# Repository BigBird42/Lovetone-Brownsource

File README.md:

# Lovetone-Brownsource

This is a kicad pcb layout for the Lovetone Brownsource guitar pedal. The original schematic can be found here: http://bmamps.com/Schematics/Effects_miscellaneous/Lovetone_BrownSource.gif.

A description for the pedal can be found here:http://www.lovetone.com/bsource.html.

I've modified the schematic to use a 10uF film cap for C2 and to include footprints for a 3PDT footswitch with an LED indicator. A Bill of Materials will be added soon. 

You can see a copy of the PCB on OSHpark here:https://oshpark.com/profiles/BigBird42.

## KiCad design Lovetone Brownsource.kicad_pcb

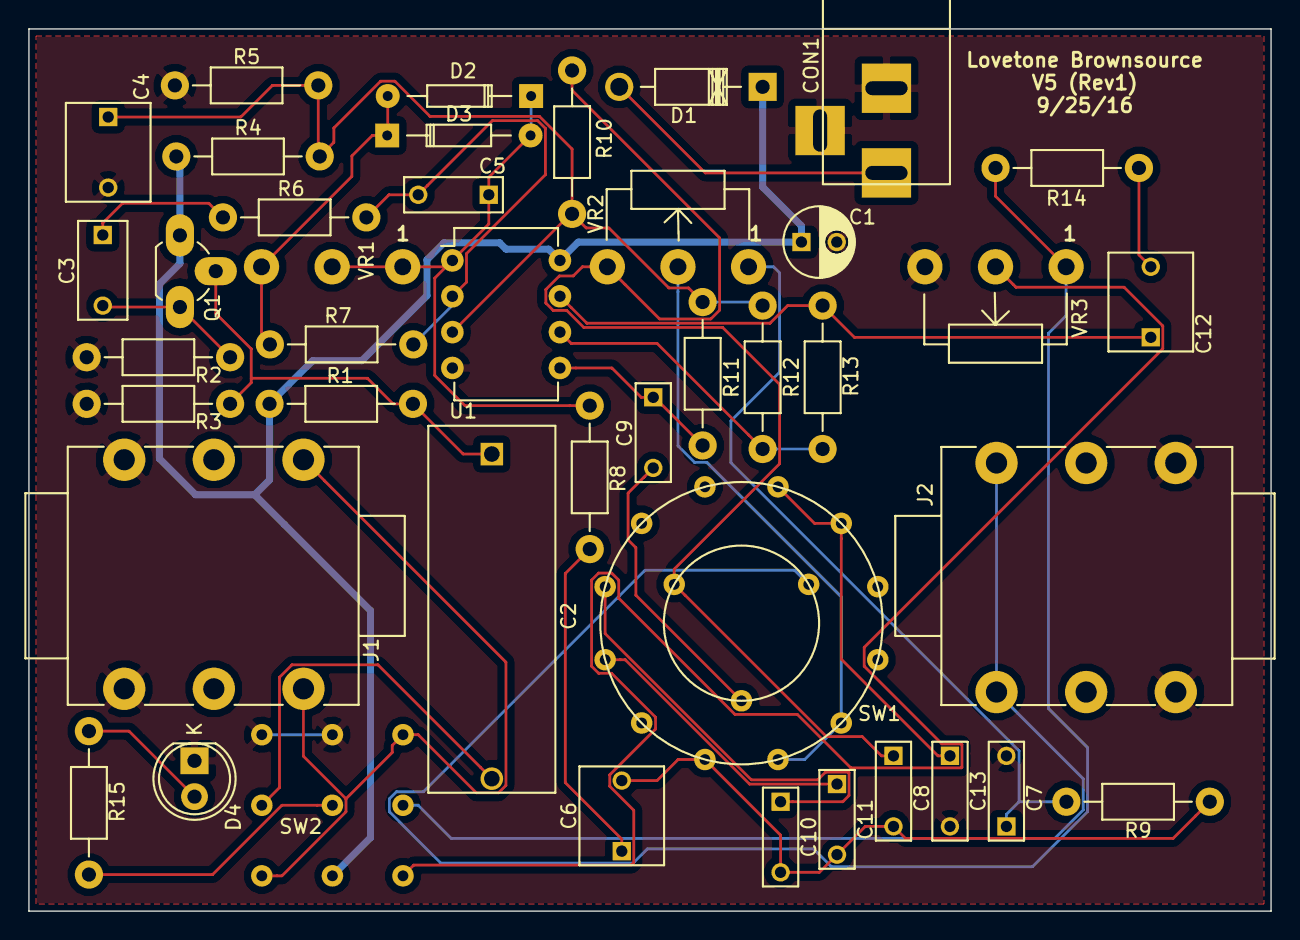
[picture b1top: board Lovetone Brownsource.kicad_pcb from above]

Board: 2 copper layers, 88.0 x 62.5 mm, 42 parts (1 on the bottom side), 30 nets.

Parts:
C1: 47uF; C_Radial_D5_L6_P2.5
C2: 10uF; C_Rect_L27_W9_H17_P23
C3: 47nF; C_Rect_L7_W3.5_P5
C4, C6, C12: 4.7uF; C_Rect_L7_W6_P5
C5, C7, C8, C10, C13: 33nF; C_Rect_L7_W2.5_P5
C9, C11: 22nF; C_Rect_L7_W2.5_P5
CON1: BARREL_JACK
D1: 1N4001; Diode_DO-41_SOD81_Horizontal_RM10
D2, D3: 1N4148; Diode_DO-35_SOD27_Horizontal_RM10
D4: LED; LED-5MM
J1, J2: JACK_TRS_6PINS; NMJ6HCD2
Q1: BC549; TO-92_Rugged
R1, R2: 1M2; Resistor_Horizontal_RM10mm
R3, R9, R10, R12: 3k9; Resistor_Horizontal_RM10mm
R4, R5, R13: 22k; Resistor_Horizontal_RM10mm
R6, R14: 220E; Resistor_Horizontal_RM10mm
R7, R8: 1k; Resistor_Horizontal_RM10mm
R11: 330k; Resistor_Horizontal_RM10mm
R15: 2k2; Resistor_Horizontal_RM10mm
SW1: Rotary_3P4T; Rotarysw0304
SW2: footsw3P2T; footsw_3PDT
U1: NE5532; DIP-8_W7.62mm
VR1: 25k; Potentiometer_WirePads
VR2: 100k; Potentiometer_WirePads
VR3: 10k; Potentiometer_WirePads

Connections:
GND: C1.2, C4.2, C7.2, C13.2, CON1.2, CON1.3, D4.1, J1.1, J1.4, J2.1, J2.4, R2.2, R3.2, R5.2, SW2.3, SW2.6, U1.4, VR3.3
unnamed: C2.1, Q1.2, R1.2, R2.1
unnamed: C2.2, SW2.2
unnamed: C3.1, R6.2
unnamed: C3.2, Q1.3, R3.1
unnamed: C4.1, R4.2, R5.1, R10.1, R11.1, R12.1, U1.3
unnamed: C5.1, D2.1, D3.2, R8.2, U1.1, VR1.1, VR1.2
unnamed: C5.2, R6.1, R7.1, U1.2
unnamed: C6.1, R8.1
unnamed: C7.1, R9.1, VR2.3
unnamed: C8.1, R10.2, SW1.1, VR2.1
unnamed: C9.1, R11.2, U1.5
unnamed: C9.2, SW1.6
unnamed: C10.1, SW1.3
unnamed: C6.2, C8.2, C10.2, C11.2, R9.2, SW1.7
unnamed: C11.1, SW1.4
unnamed: C12.1, R13.1, U1.7
unnamed: C12.2, R14.2
unnamed: C13.1, SW1.13, SW1.14
unnamed: CON1.1, D1.2
unnamed: D2.2, D3.1, R7.2, VR1.3
unnamed: D4.2, R15.1
unnamed: J1.2, J1.5, SW2.1, SW2.9
unnamed: J2.2, J2.5, SW2.8
unnamed: R12.2, R13.2, U1.6
unnamed: R14.1, SW1.11, VR3.1
unnamed: R15.2, SW2.5
unnamed: SW1.8, SW1.9, VR2.2
unnamed: SW2.7, VR3.2
VCC: C1.1, D1.1, Q1.1, R1.1, R4.1, SW2.4, U1.8

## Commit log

2016-10-03 Added description for readme
2016-10-03 edit formatting
2016-10-03 Add kicad pcb layout
